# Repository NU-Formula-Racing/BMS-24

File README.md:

# BMS-24
This repo contains all the eagle and other associated hardware files for the BMS on NFR24

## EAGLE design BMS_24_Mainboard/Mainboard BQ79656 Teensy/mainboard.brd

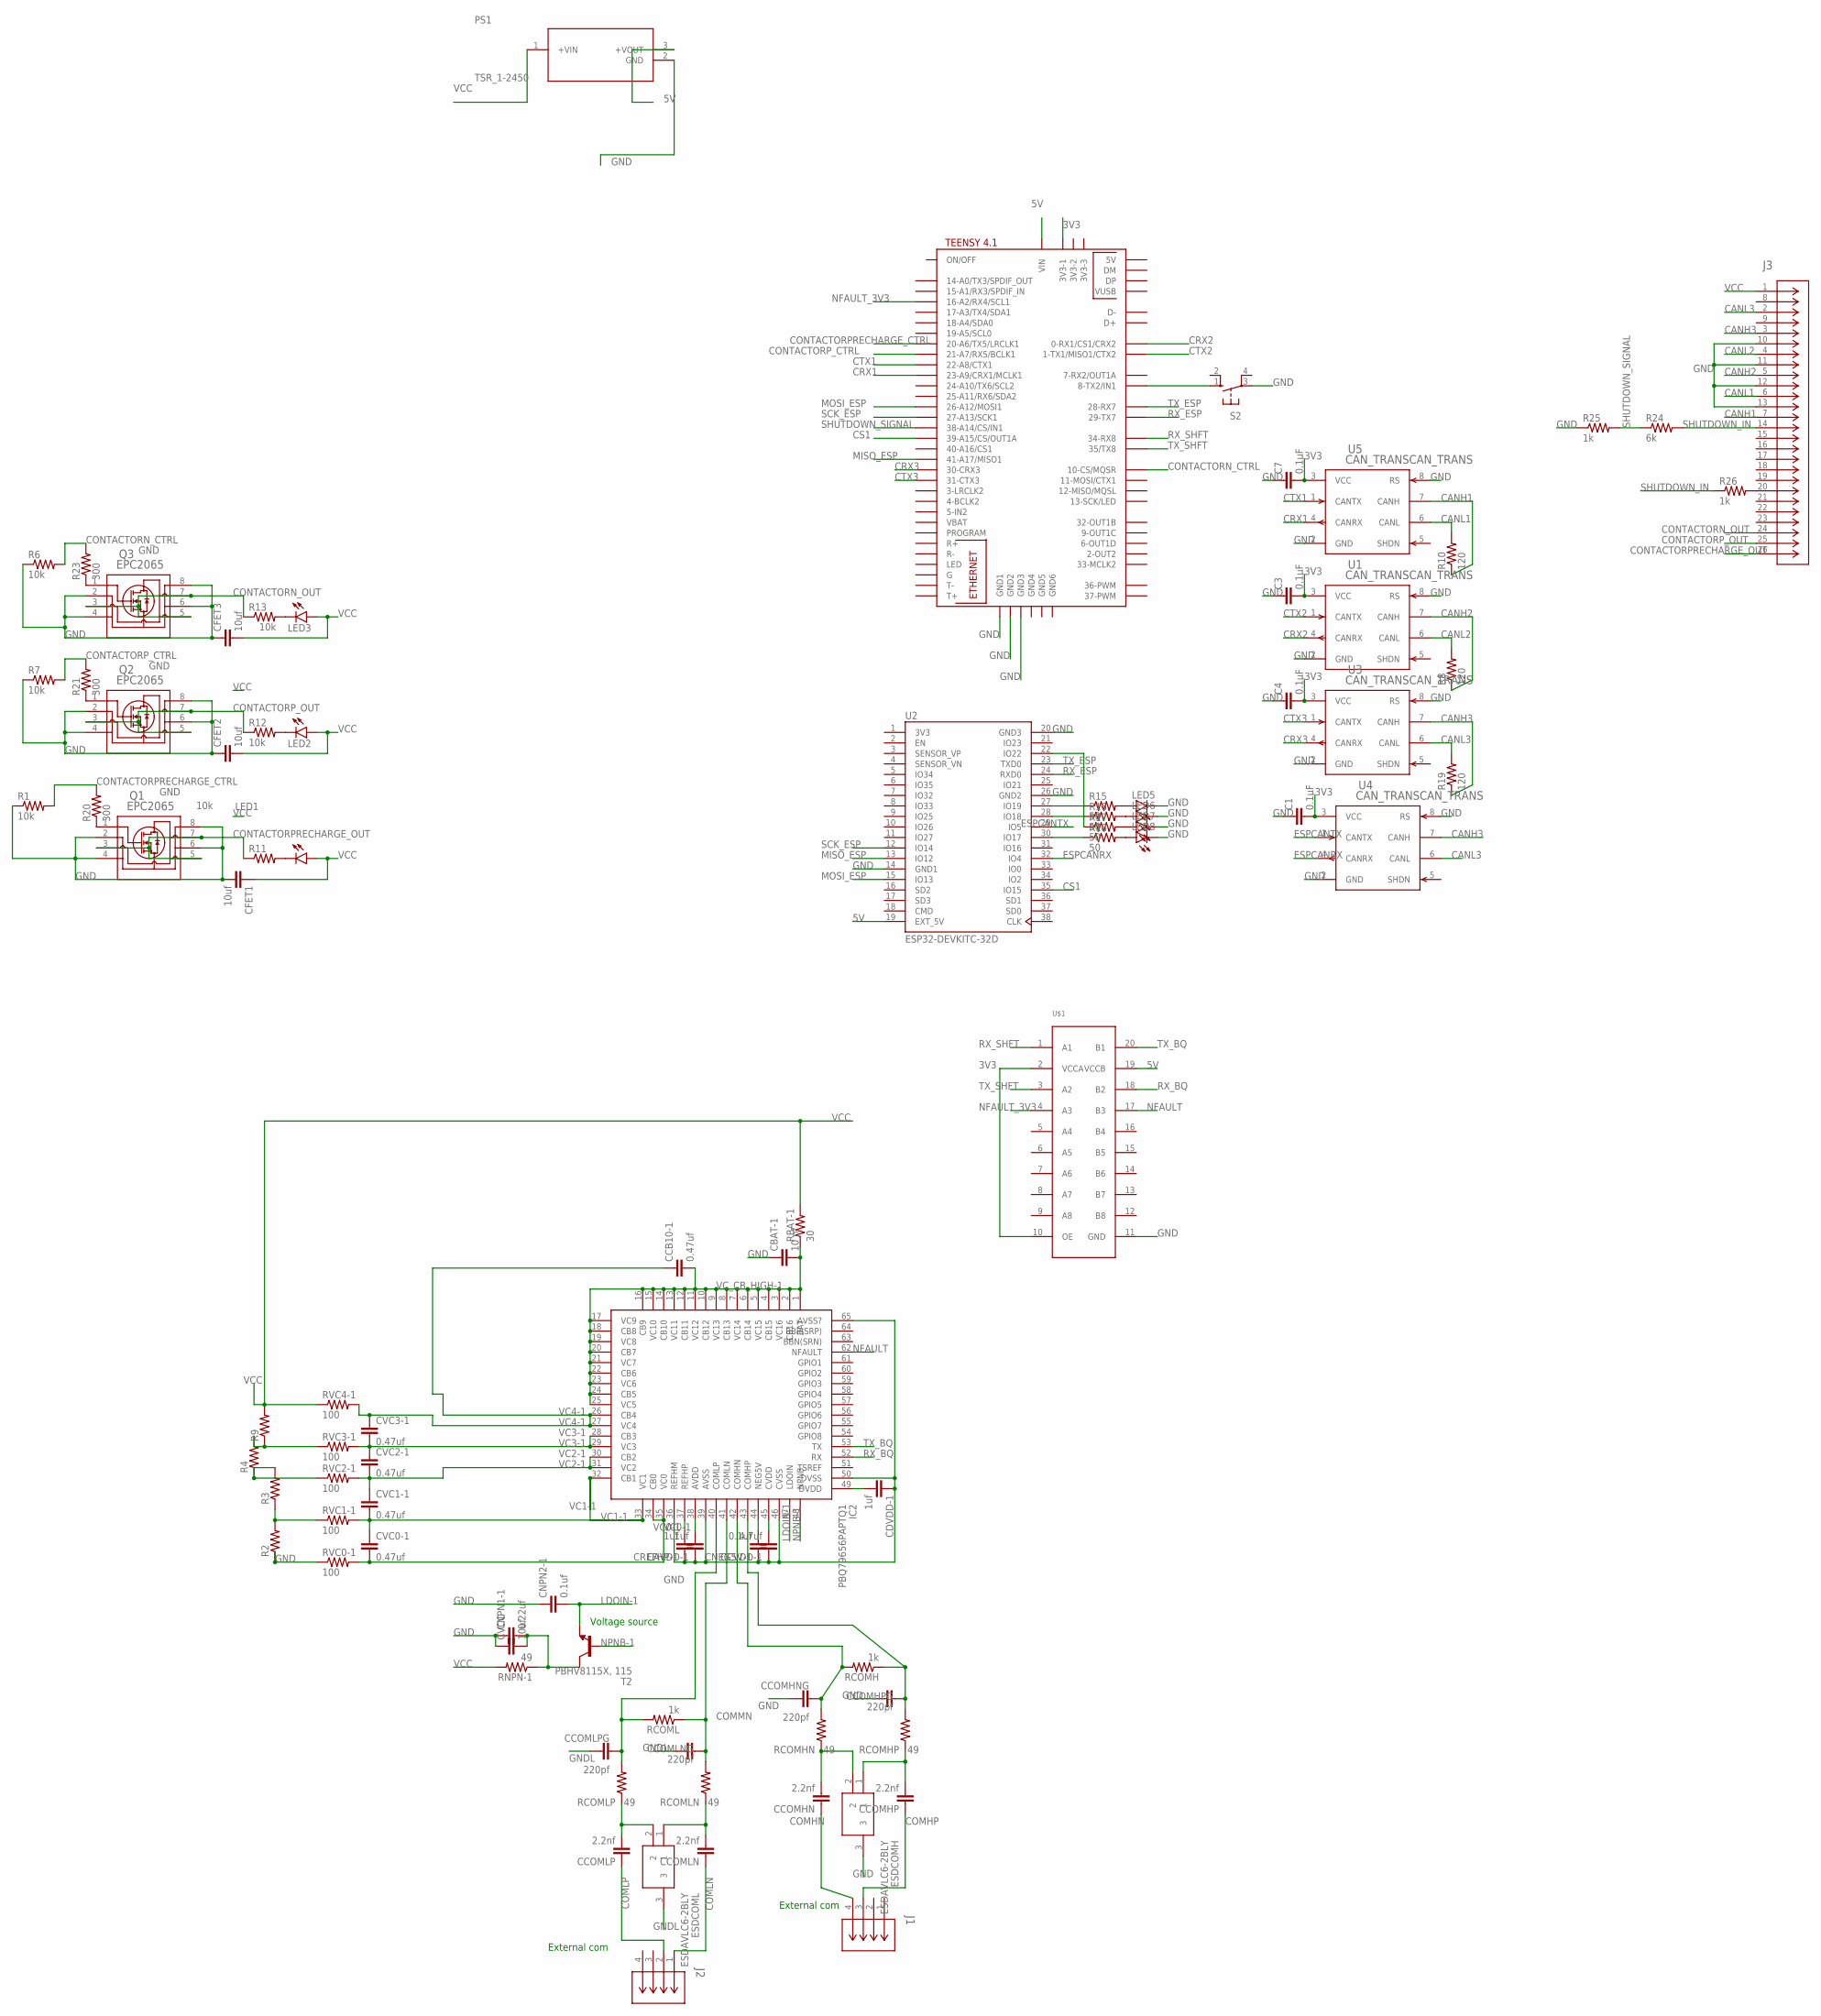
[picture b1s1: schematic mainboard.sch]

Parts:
C1, C3, C4, C7: 0.1μF; C0603
CAVDD-1: 1uf; C0603
CBAT-1: 10 nf; C0603
CCB10-1: 0.47uf; C0603
CCOMHN: 2.2nf; C075-032X103
CCOMHNG: 220pf; C0603
CCOMHP: 2.2nf; C075-032X103
CCOMHPG: 220pf; C0603
CCOMLN: 2.2nf; C075-032X103
CCOMLNG: 220pf; C0603
CCOMLP: 2.2nf; C075-032X103
CCOMLPG: 220pf; C0603
CCVDD-1: 4.7uf; C0603
CDVDD-1: 1uf; C0603
CFET1, CFET2, CFET3: 10uf; C0805
CNEG5V-1: 0.1uf; C0603
CNPN1-1: 0.22uf; C0603
CNPN2-1: 0.1uf; C0603
CREFHP-1: 1uf; C0603
CVC0-1, CVC1-1, CVC2-1, CVC3-1: 0.47uf; C0603
CVCC: 10uf; C0805
ESDCOMH: ESDAVLC6-2BLY; SOT95P255X150-3N
ESDCOML: ESDAVLC6-2BLY; SOT95P255X150-3N
IC2: PBQ79656PAPTQ1; QFP50P1200X1200X120-65N
J1, J2: DF11-4DP-2DSA(24); CON4_2X2_UF_DF11_HIR
J3: TE_AMP_SURESEAL_26; CONN26_6473423-1_TEC
LED1, LED2, LED3, LED5, LED6, LED7, LED8: LEDSML0603; SML0603
PS1: TSR_1-2450; TSR1-SINGLE_TRP
Q1, Q2, Q3: EPC2065; EPC2065_ECC
R1, R6, R7, R11, R12, R13: 10k; R0603
R2, R3, R4, R9: R-US_R0805; R0805
R8, R10, R19: 120; R0603
R15, R16, R17, R18: 50; R0603
R20, R21, R23: 300; R0603
R24: 6k; R0603
R25, R26: 1k; R0603
RBAT-1: 30; R0603
RCOMH: 1k; R0603
RCOMHN: 49; R0603
RCOMHP: 49; R0603
RCOML: 1k; R0603
RCOMLN: 49; R0603
RCOMLP: 49; R0603
RNPN-1: 49; R0603
RVC0-1, RVC1-1, RVC2-1, RVC3-1, RVC4-1: 100; R0603
S2: 10-XX; B3F-10XX
T2: PBHV8115X, 115; SOT89-BCE
U1, U3, U4, U5: CAN_TRANSCAN_TRANS; MAX3051ESA+
U2: ESP32-DEVKITC-32D; MODULE_ESP32-DEVKITC-32D
U$1: TXB0108PWSMD; TSSOP20
U$3: TEENSY41

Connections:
3V3: C1.2, C3.2, C4.2, C7.2, U1.3 (VCC), U2.1 (3V3), U3.3 (VCC), U4.3 (VCC), U5.3 (VCC), U$1.2 (VCCA), U$1.10 (OE), U$3.3V3-1
5V: PS1.3 (+VOUT), U2.19 (EXT_5V), U$1.19 (VCCB), U$3.VIN
CANH1: J3.7, R10.1, U5.7 (CANH)
CANH2: J3.5, R8.1, U1.7 (CANH)
CANH3: J3.3, R19.1, U3.7 (CANH), U4.7 (CANH)
CANL1: J3.6, R10.2, U5.6 (CANL)
CANL2: J3.4, R8.2, U1.6 (CANL)
CANL3: J3.2, R19.2, U3.6 (CANL), U4.6 (CANL)
COMHN: CCOMHN.1, J1.4
COMHP: CCOMHP.1, J1.3
COMLN: CCOMLN.1, J2.1
COMLP: CCOMLP.1, J2.2
CONTACTORN_CTRL: R6.2, R23.2, U$3.10-CS\MQSR (10-CS/MQSR)
CONTACTORN_OUT: J3.24, Q3.3, Q3.5, Q3.7, R13.1
CONTACTORPRECHARGE_CTRL: R1.2, R20.2, U$3.20-A6/TX5/LRCLK1
CONTACTORPRECHARGE_OUT: J3.26, Q1.3, Q1.5, Q1.7, R11.1
CONTACTORP_CTRL: R7.2, R21.2, U$3.21-A7/RX5/BCLK1
CONTACTORP_OUT: J3.25, Q2.3, Q2.5, Q2.7, R12.1
CRX1: U5.4 (CANRX), U$3.23-A9/CRX1/MCLK1
CRX2: U1.4 (CANRX), U$3.0-RX1/CS1/CRX2
CRX3: U3.4 (CANRX), U$3.30-CRX3
CS1: U2.35 (IO15), U$3.39-A15/CS/OUT1A
CTX1: U5.1 (CANTX), U$3.22-A8/CTX1
CTX2: U1.1 (CANTX), U$3.1-TX1/MISO1/CTX2
CTX3: U3.1 (CANTX), U$3.31-CTX3
CVDD-1: CCVDD-1.2, IC2.45 (CVDD)
ESPCANRX: U2.32 (IO4), U4.4 (CANRX)
ESPCANTX: U2.29 (IO5), U4.1 (CANTX)
GND: C1.1, C3.1, C4.1, C7.1, CAVDD-1.1, CBAT-1.1, CCOMHNG.1, CCOMHPG.1, CCVDD-1.1, CDVDD-1.1, CFET1.2, CFET2.1, CFET3.1, CNEG5V-1.1, CNPN1-1.1, CNPN2-1.1, CREFHP-1.1, CVCC.1, ESDCOMH.3, IC2.36 (REFHM), IC2.39 (AVSS), IC2.46 (CVSS), IC2.50 (DVSS), IC2.65 (AVSS?), J3.10, J3.11, J3.12, J3.13, LED5.C, LED6.C, LED7.C, LED8.C, PS1.2 (GND), Q1.2, Q1.4, Q1.6, Q1.8, Q2.2, Q2.4, Q2.6, Q2.8, Q3.2, Q3.4, Q3.6, Q3.8, R1.1, R2.1, R6.1, R7.1, R25.1, RVC0-1.1, S2.3, U1.2 (GND), U1.8 (RS), U2.14 (GND1), U2.20 (GND3), U2.26 (GND2), U3.2 (GND), U3.8 (RS), U4.2 (GND), U4.8 (RS), U5.2 (GND), U5.8 (RS), U$1.11 (GND), U$3.GND1, U$3.GND2, U$3.GND3
GNDL: CCOMLNG.1, CCOMLPG.1, ESDCOML.3
LDOIN-1: CNPN2-1.2, IC2.47 (LDOIN), T2.E
MISO_ESP: U2.13 (IO12), U$3.41-A17/MISO1
MOSI_ESP: U2.15 (IO13), U$3.26-A12/MOSI1
unnamed: CCOMHP.2, ESDCOMH.1, RCOMHP.1
unnamed: J3.20, R26.2
unnamed: LED3.C, R13.2
unnamed: S2.1 (S), U$3.8-TX2/IN1
unnamed: CCOMHN.2, ESDCOMH.2, RCOMHN.1
unnamed: LED2.C, R12.2
unnamed: CCOMLNG.2, IC2.41 (COMLN), RCOML.1, RCOMLN.2
unnamed: R17.1, U2.22 (IO22)
unnamed: LED1.C, R11.2
unnamed: Q1.1, R20.1
unnamed: Q2.1, R21.1
unnamed: R15.1, U2.27 (IO19)
unnamed: R16.1, U2.28 (IO18)
unnamed: Q3.1, R23.1
unnamed: R18.1, U2.30 (IO17)
unnamed: LED5.A, R15.2
unnamed: LED6.A, R16.2
unnamed: LED7.A, R17.2
unnamed: LED8.A, R18.2
unnamed: CCOMLPG.2, IC2.40 (COMLP), RCOML.2, RCOMLP.2
unnamed: CCOMLP.2, ESDCOML.2, RCOMLP.1
unnamed: CCOMLN.2, ESDCOML.1, RCOMLN.1
unnamed: R3.2, R4.1, RVC2-1.1
unnamed: R2.2, R3.1, RVC1-1.1
unnamed: R4.2, R9.1, RVC3-1.1
unnamed: CREFHP-1.2, IC2.37 (REFHP)
unnamed: CAVDD-1.2, IC2.38 (AVDD)
unnamed: CNEG5V-1.2, IC2.44 (NEG5V)
unnamed: CDVDD-1.2, IC2.49 (DVDD)
unnamed: CNPN1-1.2, CVCC.2, RNPN-1.1, T2.C
unnamed: CCOMHPG.2, IC2.43 (COMHP), RCOMH.1, RCOMHP.2
unnamed: CCOMHNG.2, IC2.42 (COMHN), RCOMH.2, RCOMHN.2
NFAULT: IC2.62 (NFAULT), U$1.17 (B3)
NFAULT_3V3: U$1.4 (A3), U$3.16-A2/RX4/SCL1
NPNB-1: IC2.48 (NPNB), T2.B
RX_BQ: IC2.52 (RX), U$1.18 (B2)
RX_ESP: U2.24 (RXD0), U$3.29-TX7
RX_SHFT: U$1.1 (A1), U$3.34-RX8
SCK_ESP: U2.12 (IO14), U$3.27-A13/SCK1
SHUTDOWN_IN: J3.14, R24.2, R26.1
SHUTDOWN_SIGNAL: R24.1, R25.2, U$3.38-A14/CS/IN1
TX_BQ: IC2.53 (TX), U$1.20 (B1)
TX_ESP: U2.23 (TXD0), U$3.28-RX7
TX_SHFT: U$1.3 (A2), U$3.35-TX8 (35/TX8)
VC0-1: CVC0-1.2, IC2.34 (CB0), IC2.35 (VC0), RVC0-1.2
VC1-1: CVC0-1.1, CVC1-1.2, IC2.32 (CB1), IC2.33 (VC1), RVC1-1.2
VC2-1: CVC1-1.1, CVC2-1.2, IC2.30 (CB2), IC2.31 (VC2), RVC2-1.2
VC3-1: CVC2-1.1, CVC3-1.2, IC2.28 (CB3), IC2.29 (VC3), RVC3-1.2
VC4-1: CCB10-1.1, CVC3-1.1, IC2.26 (CB4), IC2.27 (VC4), RVC4-1.2
VCC: CFET1.1, CFET2.2, CFET3.2, J3.1, LED1.A, LED2.A, LED3.A, PS1.1 (+VIN), R9.2, RBAT-1.2, RNPN-1.2, RVC4-1.1
VC_CB_HIGH-1: CBAT-1.2, CCB10-1.2, IC2.1 (BAT), IC2.2 (CB16), IC2.3 (VC16), IC2.4 (CB15), IC2.5 (VC15), IC2.6 (CB14), IC2.7 (VC14), IC2.8 (CB13), IC2.9 (VC13), IC2.10 (CB12), IC2.11 (VC12), IC2.12 (CB11), IC2.13 (VC11), IC2.14 (CB10), IC2.15 (VC10), IC2.16 (CB9), IC2.17 (VC9), IC2.18 (CB8), IC2.19 (VC8), IC2.20 (CB7), IC2.21 (VC7), IC2.22 (CB6), IC2.23 (VC6), IC2.24 (CB5), IC2.25 (VC5), RBAT-1.1

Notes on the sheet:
External com
Voltage source

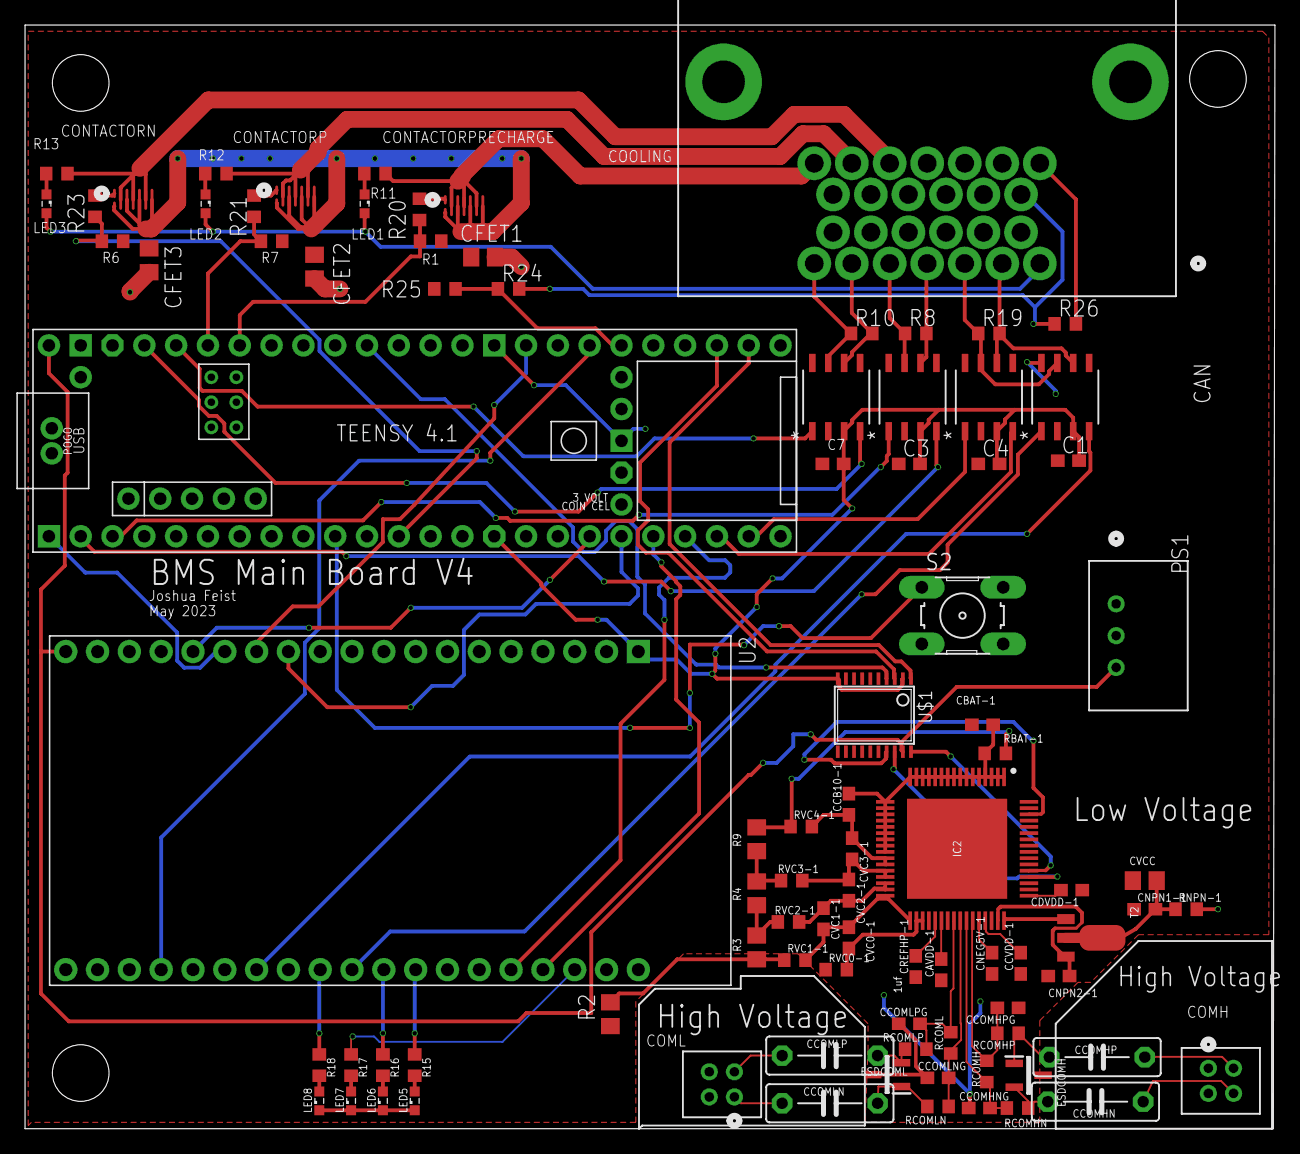
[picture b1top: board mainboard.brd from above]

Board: 2 copper layers, 99.8 x 88.1 mm, 91 parts (0 on the bottom side), 84 nets.

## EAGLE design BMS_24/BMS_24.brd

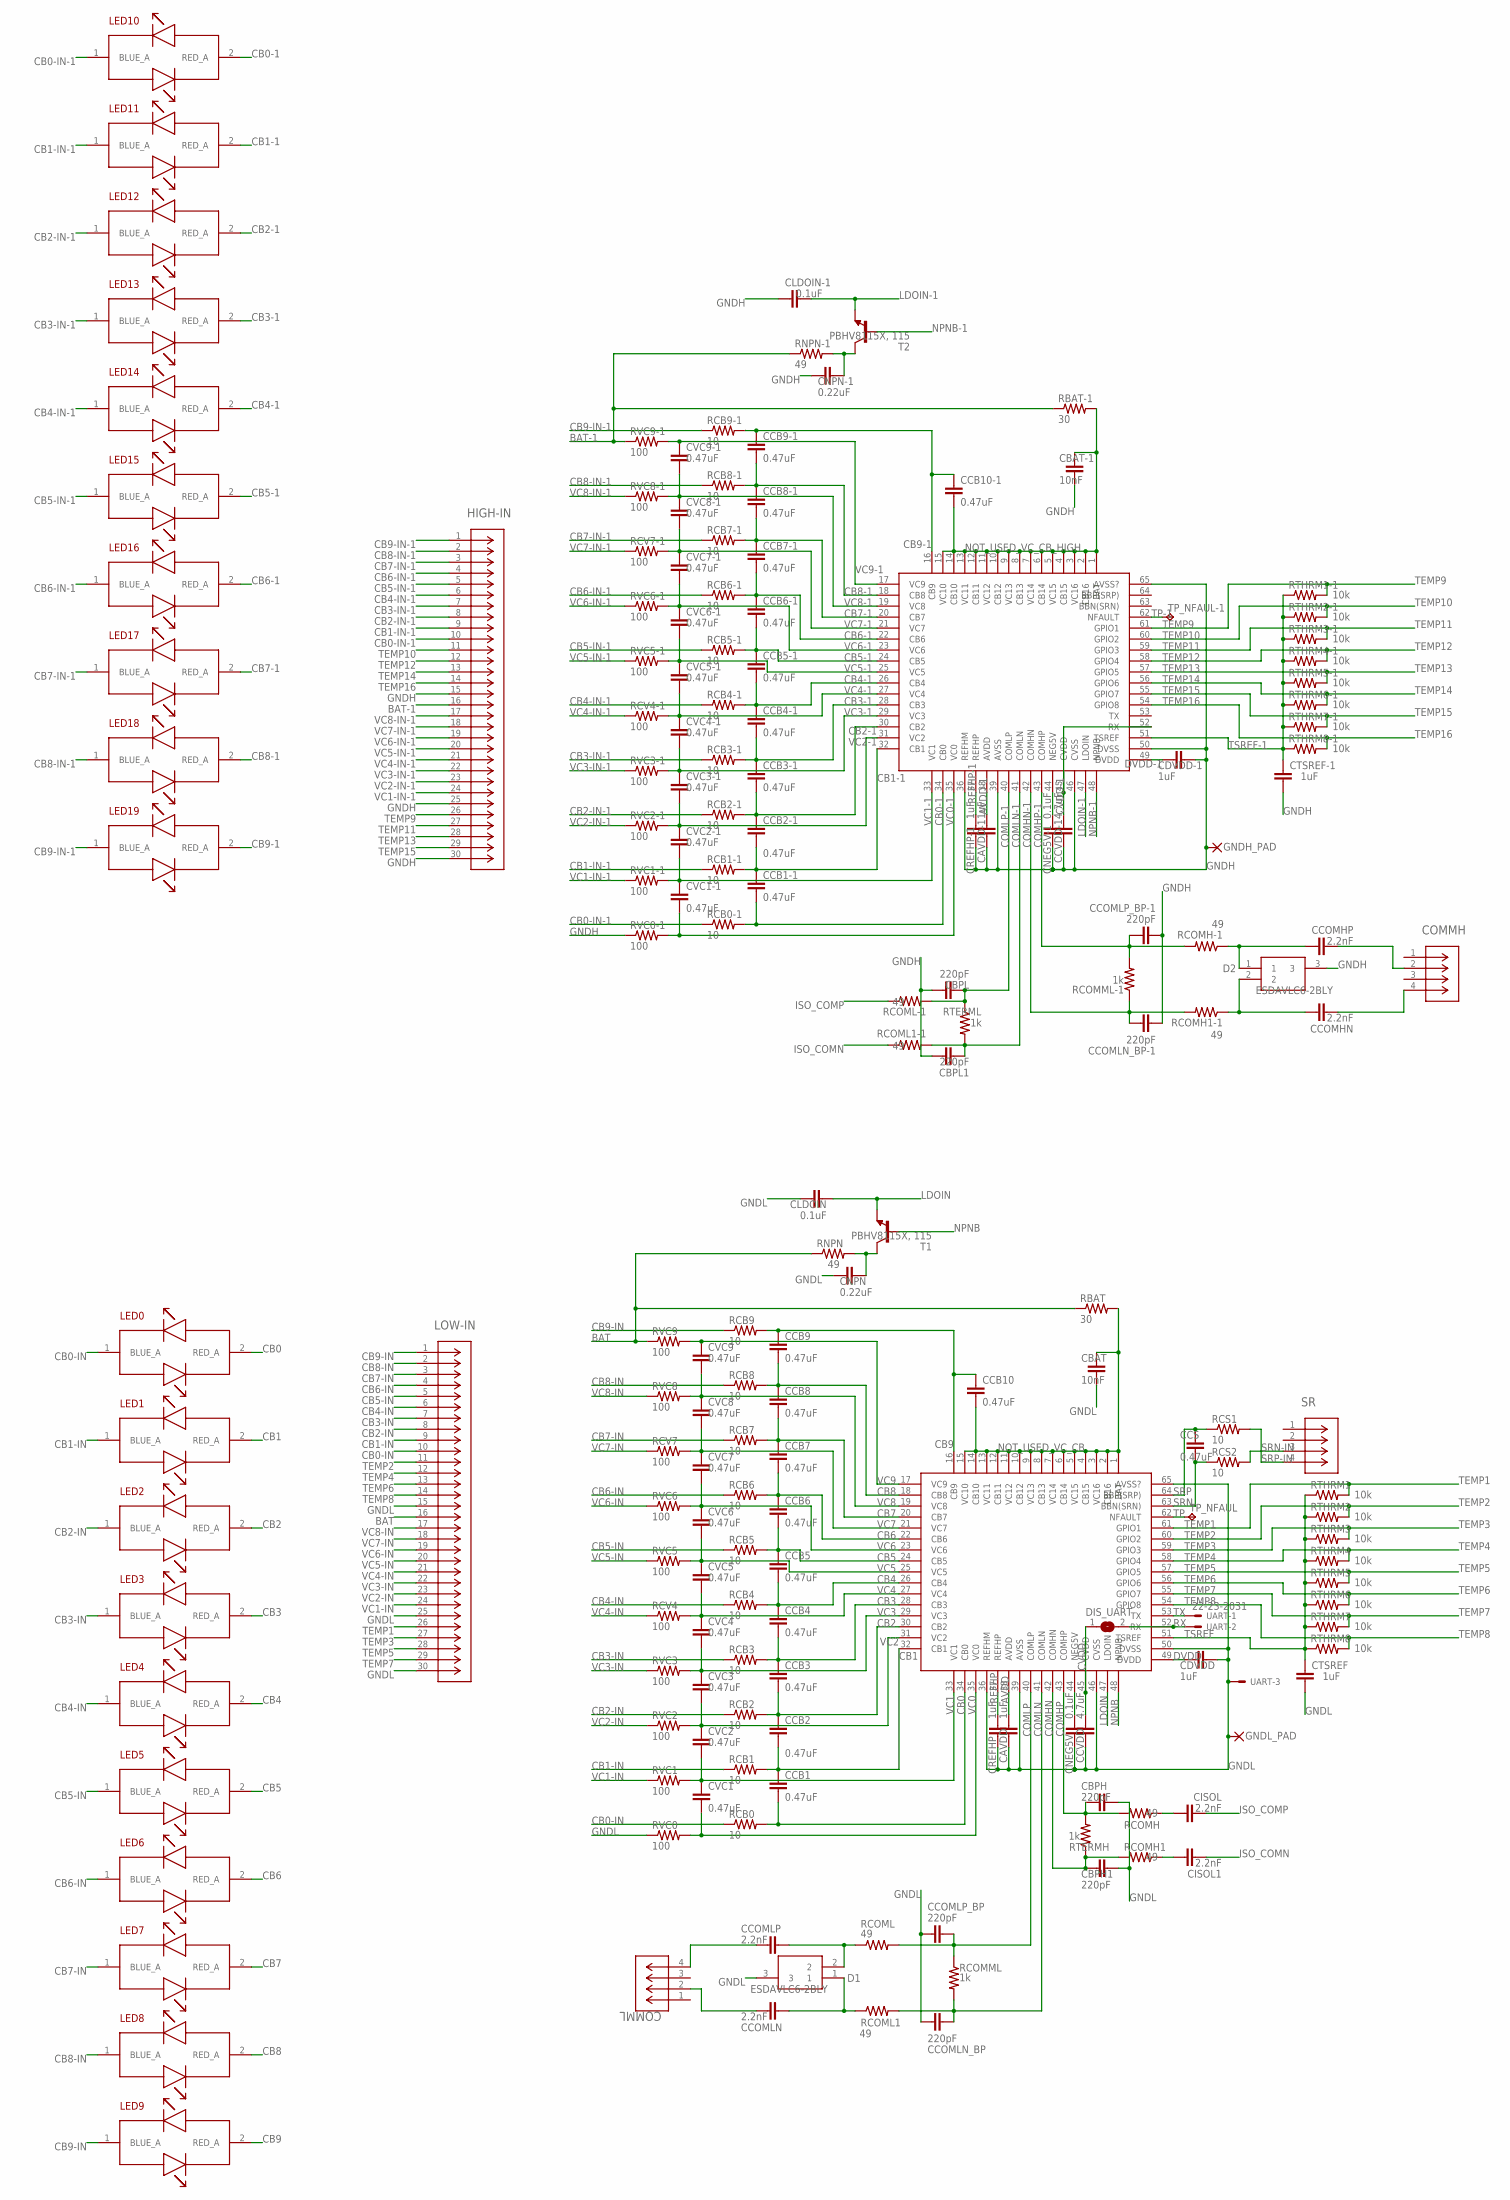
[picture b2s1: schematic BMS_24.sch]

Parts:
CAVDD: 1uF; C0603
CAVDD-1: 1uF; C0603
CBAT: 10nF; C0603
CBAT-1: 10nF; C0603
CBPH, CBPH1: 220pF; C0603
CBPL, CBPL1: 220pF; C0603
CCB1, CCB1-1, CCB2, CCB2-1, CCB3, CCB3-1, CCB4, CCB4-1, CCB5, CCB5-1, CCB6, CCB6-1, CCB7, CCB7-1, CCB8, CCB8-1, CCB9, CCB9-1, CCB10, CCB10-1: 0.47uF; C0603
CCOMHN: 2.2nF; C0603
CCOMHP: 2.2nF; C0603
CCOMLN: 2.2nF; C0603
CCOMLN_BP: 220pF; C0603
CCOMLN_BP-1: 220pF; C0603
CCOMLP: 2.2nF; C0603
CCOMLP_BP: 220pF; C0603
CCOMLP_BP-1: 220pF; C0603
CCS: 0.47uF; C0603
CCVDD: 4.7uF; C0603
CCVDD-1: 4.7uF; C0603
CDVDD: 1uF; C0603
CDVDD-1: 1uF; C0603
CISOL, CISOL1: 2.2nF; C0603
CLDOIN: 0.1uF; C0603
CLDOIN-1: 0.1uF; C0603
CNEG5V, CNEG5V-1: 0.1uF; C0603
CNPN: 0.22uF; C0603
CNPN-1: 0.22uF; C0603
COMMH: DF11-4DP-2DSA(24); CON4_2X2_UF_DF11_HIR
COMML: DF11-4DP-2DSA(24); CON4_2X2_UF_DF11_HIR
CREFHP: 1uF; C0603
CREFHP-1: 1uF; C0603
CTSREF: 1uF; C0603
CTSREF-1: 1uF; C0603
CVC1, CVC1-1, CVC2, CVC2-1, CVC3, CVC3-1, CVC4, CVC4-1, CVC5, CVC5-1, CVC6, CVC6-1, CVC7, CVC7-1, CVC8, CVC8-1, CVC9, CVC9-1: 0.47uF; C0603
D1, D2: ESDAVLC6-2BLY; SOT95P255X150-3N
DIS_UART: SJ
GNDH_PAD: SMD2; SMD1,27-2,54
GNDL_PAD: SMD2; SMD1,27-2,54
HIGH-IN: 87606-315LF; 87606-315LF_AMP
IC1, IC2: PBQ79656PAPTQ1; QFP50P1200X1200X120-65N
LED0, LED1, LED2, LED3, LED4, LED5, LED6, LED7, LED8, LED9, LED10, LED11, LED12, LED13, LED14, LED15, LED16, LED17, LED18, LED19: TJ-S1608SW6TNPGLCRB-A5
LOW-IN: 87606-315LF; 87606-315LF_AMP
RBAT: 30; R0603
RBAT-1: 30; R0603
RCB0, RCB0-1, RCB1, RCB1-1, RCB2, RCB2-1, RCB3, RCB3-1, RCB4, RCB4-1, RCB5, RCB5-1, RCB6, RCB6-1, RCB7, RCB7-1, RCB8, RCB8-1, RCB9, RCB9-1: 10; R1210
RCOMH, RCOMH1, RCOMH1-1: 49; R0603
RCOMH-1: 49; R0603
RCOML, RCOML1, RCOML1-1: 49; R0603
RCOML-1: 49; R0603
RCOMML: 1k; R0603
RCOMML-1: 1k; R0603
RCS1, RCS2: 10; R0603
RCV4, RCV4-1, RCV7, RCV7-1: 100; R0603
RNPN: 49; R0603
RNPN-1: 49; R0603
RTERMH: 1k; R0603
RTERML: 1k; R0603
RTHRM1, RTHRM1-1, RTHRM2, RTHRM2-1, RTHRM3, RTHRM3-1, RTHRM4, RTHRM4-1, RTHRM5, RTHRM5-1, RTHRM6, RTHRM6-1, RTHRM7, RTHRM7-1, RTHRM8, RTHRM8-1: 10k; R0603
RVC0, RVC0-1, RVC1, RVC1-1, RVC2, RVC2-1, RVC3, RVC3-1, RVC5, RVC5-1, RVC6, RVC6-1, RVC8, RVC8-1, RVC9, RVC9-1: 100; R0603
SR: DF11-4DP-2DSA(24); CON4_2X2_UF_DF11_HIR
T1, T2: PBHV8115X, 115; SOT89-BCE
TP_NFAUL: TPB2,54; B2,54
TP_NFAUL-1: TPB2,54; B2,54
UART: 22-23-2031

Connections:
AVDD: CAVDD.1, IC2.38 (AVDD)
AVDD-1: CAVDD-1.1, IC1.38 (AVDD)
BAT: LOW-IN.16, RBAT.1, RNPN.1, RVC9.1
BAT-1: HIGH-IN.16, RBAT-1.1, RNPN-1.1, RVC9-1.1
CB0: CCB1.2, IC2.34 (CB0), LED0.2 (RED_A), RCB0.2
CB0-1: CCB1-1.2, IC1.34 (CB0), LED10.2 (RED_A), RCB0-1.2
CB0-IN: LED0.1 (BLUE_A), LOW-IN.10, RCB0.1
CB0-IN-1: HIGH-IN.10, LED10.1 (BLUE_A), RCB0-1.1
CB1: CCB1.1, CCB2.2, IC2.32 (CB1), LED1.2 (RED_A), RCB1.2
CB1-1: CCB1-1.1, CCB2-1.2, IC1.32 (CB1), LED11.2 (RED_A), RCB1-1.2
CB1-IN: LED1.1 (BLUE_A), LOW-IN.9, RCB1.1
CB1-IN-1: HIGH-IN.9, LED11.1 (BLUE_A), RCB1-1.1
CB2: CCB2.1, CCB3.2, IC2.30 (CB2), LED2.2 (RED_A), RCB2.2
CB2-1: CCB2-1.1, CCB3-1.2, IC1.30 (CB2), LED12.2 (RED_A), RCB2-1.2
CB2-IN: LED2.1 (BLUE_A), LOW-IN.8, RCB2.1
CB2-IN-1: HIGH-IN.8, LED12.1 (BLUE_A), RCB2-1.1
CB3: CCB3.1, CCB4.2, IC2.28 (CB3), LED3.2 (RED_A), RCB3.2
CB3-1: CCB3-1.1, CCB4-1.2, IC1.28 (CB3), LED13.2 (RED_A), RCB3-1.2
CB3-IN: LED3.1 (BLUE_A), LOW-IN.7, RCB3.1
CB3-IN-1: HIGH-IN.7, LED13.1 (BLUE_A), RCB3-1.1
CB4: CCB4.1, CCB5.2, IC2.26 (CB4), LED4.2 (RED_A), RCB4.2
CB4-1: CCB4-1.1, CCB5-1.2, IC1.26 (CB4), LED14.2 (RED_A), RCB4-1.2
CB4-IN: LED4.1 (BLUE_A), LOW-IN.6, RCB4.1
CB4-IN-1: HIGH-IN.6, LED14.1 (BLUE_A), RCB4-1.1
CB5: CCB5.1, CCB6.2, IC2.24 (CB5), LED5.2 (RED_A), RCB5.2
CB5-1: CCB5-1.1, CCB6-1.2, IC1.24 (CB5), LED15.2 (RED_A), RCB5-1.2
CB5-IN: LED5.1 (BLUE_A), LOW-IN.5, RCB5.1
CB5-IN-1: HIGH-IN.5, LED15.1 (BLUE_A), RCB5-1.1
CB6: CCB6.1, CCB7.2, IC2.22 (CB6), LED6.2 (RED_A), RCB6.2
CB6-1: CCB6-1.1, CCB7-1.2, IC1.22 (CB6), LED16.2 (RED_A), RCB6-1.2
CB6-IN: LED6.1 (BLUE_A), LOW-IN.4, RCB6.1
CB6-IN-1: HIGH-IN.4, LED16.1 (BLUE_A), RCB6-1.1
CB7: CCB7.1, CCB8.2, IC2.20 (CB7), LED7.2 (RED_A), RCB7.2
CB7-1: CCB7-1.1, CCB8-1.2, IC1.20 (CB7), LED17.2 (RED_A), RCB7-1.2
CB7-IN: LED7.1 (BLUE_A), LOW-IN.3, RCB7.1
CB7-IN-1: HIGH-IN.3, LED17.1 (BLUE_A), RCB7-1.1
CB8: CCB8.1, CCB9.2, IC2.18 (CB8), LED8.2 (RED_A), RCB8.2
CB8-1: CCB8-1.1, CCB9-1.2, IC1.18 (CB8), LED18.2 (RED_A), RCB8-1.2
CB8-IN: LED8.1 (BLUE_A), LOW-IN.2, RCB8.1
CB8-IN-1: HIGH-IN.2, LED18.1 (BLUE_A), RCB8-1.1
CB9: CCB9.1, CCB10.2, IC2.16 (CB9), LED9.2 (RED_A), RCB9.2
CB9-1: CCB9-1.1, CCB10-1.2, IC1.16 (CB9), LED19.2 (RED_A), RCB9-1.2
CB9-IN: LED9.1 (BLUE_A), LOW-IN.1, RCB9.1
CB9-IN-1: HIGH-IN.1, LED19.1 (BLUE_A), RCB9-1.1
COMHN: CBPH1.1, IC2.42 (COMHN), RCOMH1.2, RTERMH.1
COMHN-1: CCOMLN_BP-1.1, IC1.42 (COMHN), RCOMH1-1.2, RCOMML-1.1
COMHP: CBPH.1, IC2.43 (COMHP), RCOMH.2, RTERMH.2
COMHP-1: CCOMLP_BP-1.1, IC1.43 (COMHP), RCOMH-1.2, RCOMML-1.2
COMLN: CCOMLN_BP.1, IC2.41 (COMLN), RCOML1.2, RCOMML.2
COMLN-1: CBPL1.1, IC1.41 (COMLN), RCOML1-1.2, RTERML.2
COMLP: CCOMLP_BP.1, IC2.40 (COMLP), RCOML.2, RCOMML.1
COMLP-1: CBPL.1, IC1.40 (COMLP), RCOML-1.2, RTERML.1
CVDD: CCVDD.1, DIS_UART.1, IC2.45 (CVDD)
CVDD-1: CCVDD-1.1, IC1.45 (CVDD), IC1.52 (RX)
DVDD: CDVDD.1, IC2.49 (DVDD)
DVDD-1: CDVDD-1.1, IC1.49 (DVDD)
GNDH: CAVDD-1.2, CBAT-1.1, CBPL.2, CBPL1.2, CCOMLN_BP-1.2, CCOMLP_BP-1.2, CCVDD-1.2, CDVDD-1.2, CLDOIN-1.2, CNEG5V-1.2, CNPN-1.1, CREFHP-1.2, CTSREF-1.2, D2.3, GNDH_PAD.1, HIGH-IN.15, HIGH-IN.25, HIGH-IN.30, IC1.36 (REFHM), IC1.39 (AVSS), IC1.46 (CVSS), IC1.50 (DVSS), IC1.65 (AVSS?), RVC0-1.1
GNDL: CAVDD.2, CBAT.1, CBPH.2, CBPH1.2, CCOMLN_BP.2, CCOMLP_BP.2, CCVDD.2, CDVDD.2, CLDOIN.2, CNEG5V.2, CNPN.1, CREFHP.2, CTSREF.2, D1.3, GNDL_PAD.1, IC2.36 (REFHM), IC2.39 (AVSS), IC2.46 (CVSS), IC2.50 (DVSS), IC2.65 (AVSS?), LOW-IN.15, LOW-IN.25, LOW-IN.30, RVC0.1, UART.3
ISO_COMN: CISOL1.1, RCOML1-1.1
ISO_COMP: CISOL.1, RCOML-1.1
LDOIN: CLDOIN.1, IC2.47 (LDOIN), T1.E
LDOIN-1: CLDOIN-1.1, IC1.47 (LDOIN), T2.E
unnamed: CNPN.2, RNPN.2, T1.C
unnamed: CNEG5V.1, IC2.44 (NEG5V)
unnamed: CISOL.2, RCOMH.1
unnamed: CISOL1.2, RCOMH1.1
unnamed: CCOMLN.2, D1.1, RCOML1.1
unnamed: CCOMLP.2, D1.2, RCOML.1
unnamed: CNEG5V-1.1, IC1.44 (NEG5V)
unnamed: CNPN-1.2, RNPN-1.2, T2.C
unnamed: CCOMHP.2, D2.1, RCOMH-1.1
unnamed: CCOMHN.2, D2.2, RCOMH1-1.1
unnamed: CCOMHP.1, COMMH.2
unnamed: CCOMHN.1, COMMH.4
unnamed: CCOMLN.1, COMML.2
unnamed: CCOMLP.1, COMML.4
NOT_USED_VC_CB: CBAT.2, CCB10.1, IC2.1 (BAT), IC2.2 (CB16), IC2.3 (VC16), IC2.4 (CB15), IC2.5 (VC15), IC2.6 (CB14), IC2.7 (VC14), IC2.8 (CB13), IC2.9 (VC13), IC2.10 (CB12), IC2.11 (VC12), IC2.12 (CB11), IC2.13 (VC11), IC2.14 (CB10), IC2.15 (VC10), RBAT.2
NOT_USED_VC_CB_HIGH: CBAT-1.2, CCB10-1.1, IC1.1 (BAT), IC1.2 (CB16), IC1.3 (VC16), IC1.4 (CB15), IC1.5 (VC15), IC1.6 (CB14), IC1.7 (VC14), IC1.8 (CB13), IC1.9 (VC13), IC1.10 (CB12), IC1.11 (VC12), IC1.12 (CB11), IC1.13 (VC11), IC1.14 (CB10), IC1.15 (VC10), RBAT-1.2
NPNB: IC2.48 (NPNB), T1.B
NPNB-1: IC1.48 (NPNB), T2.B
REFHP: CREFHP.1, IC2.37 (REFHP)
REFHP-1: CREFHP-1.1, IC1.37 (REFHP)
RX: DIS_UART.2, IC2.52 (RX), UART.2
SRN: CCS.1, IC2.63 (BBN(SRN)), RCS2.1
SRN-IN: RCS2.2, SR.3
SRP: CCS.2, IC2.64 (BBP(SRP)), RCS1.1
SRP-IN: RCS1.2, SR.4
TEMP1: IC2.61 (GPIO1), LOW-IN.26, RTHRM1.2
TEMP2: IC2.60 (GPIO2), LOW-IN.11, RTHRM2.2
TEMP3: IC2.59 (GPIO3), LOW-IN.27, RTHRM3.2
TEMP4: IC2.58 (GPIO4), LOW-IN.12, RTHRM4.2
TEMP5: IC2.57 (GPIO5), LOW-IN.28, RTHRM5.2
TEMP6: IC2.56 (GPIO6), LOW-IN.13, RTHRM6.2
TEMP7: IC2.55 (GPIO7), LOW-IN.29, RTHRM7.2
TEMP8: IC2.54 (GPIO8), LOW-IN.14, RTHRM8.2
TEMP9: HIGH-IN.26, IC1.61 (GPIO1), RTHRM1-1.2
TEMP10: HIGH-IN.11, IC1.60 (GPIO2), RTHRM2-1.2
TEMP11: HIGH-IN.27, IC1.59 (GPIO3), RTHRM3-1.2
TEMP12: HIGH-IN.12, IC1.58 (GPIO4), RTHRM4-1.2
TEMP13: HIGH-IN.28, IC1.57 (GPIO5), RTHRM5-1.2
TEMP14: HIGH-IN.13, IC1.56 (GPIO6), RTHRM6-1.2
TEMP15: HIGH-IN.29, IC1.55 (GPIO7), RTHRM7-1.2
TEMP16: HIGH-IN.14, IC1.54 (GPIO8), RTHRM8-1.2
TP: IC2.62 (NFAULT), TP_NFAUL.TP
TP-1: IC1.62 (NFAULT), TP_NFAUL-1.TP
TSREF: CTSREF.1, IC2.51 (TSREF), RTHRM1.1, RTHRM2.1, RTHRM3.1, RTHRM4.1, RTHRM5.1, RTHRM6.1, RTHRM7.1, RTHRM8.1
TSREF-1: CTSREF-1.1, IC1.51 (TSREF), RTHRM1-1.1, RTHRM2-1.1, RTHRM3-1.1, RTHRM4-1.1, RTHRM5-1.1, RTHRM6-1.1, RTHRM7-1.1, RTHRM8-1.1
TX: IC2.53 (TX), UART.1
VC0: CVC1.2, IC2.35 (VC0), RVC0.2
VC0-1: CVC1-1.2, IC1.35 (VC0), RVC0-1.2
VC1: CVC1.1, CVC2.2, IC2.33 (VC1), RVC1.2
VC1-1: CVC1-1.1, CVC2-1.2, IC1.33 (VC1), RVC1-1.2
VC1-IN: LOW-IN.24, RVC1.1
VC1-IN-1: HIGH-IN.24, RVC1-1.1
VC2: CVC2.1, CVC3.2, IC2.31 (VC2), RVC2.2
VC2-1: CVC2-1.1, CVC3-1.2, IC1.31 (VC2), RVC2-1.2
VC2-IN: LOW-IN.23, RVC2.1
VC2-IN-1: HIGH-IN.23, RVC2-1.1
VC3: CVC3.1, CVC4.2, IC2.29 (VC3), RVC3.2
VC3-1: CVC3-1.1, CVC4-1.2, IC1.29 (VC3), RVC3-1.2
VC3-IN: LOW-IN.22, RVC3.1
VC3-IN-1: HIGH-IN.22, RVC3-1.1
VC4: CVC4.1, CVC5.2, IC2.27 (VC4), RCV4.2
VC4-1: CVC4-1.1, CVC5-1.2, IC1.27 (VC4), RCV4-1.2
VC4-IN: LOW-IN.21, RCV4.1
VC4-IN-1: HIGH-IN.21, RCV4-1.1
VC5: CVC5.1, CVC6.2, IC2.25 (VC5), RVC5.2
VC5-1: CVC5-1.1, CVC6-1.2, IC1.25 (VC5), RVC5-1.2
VC5-IN: LOW-IN.20, RVC5.1
VC5-IN-1: HIGH-IN.20, RVC5-1.1
VC6: CVC6.1, CVC7.2, IC2.23 (VC6), RVC6.2
VC6-1: CVC6-1.1, CVC7-1.2, IC1.23 (VC6), RVC6-1.2
VC6-IN: LOW-IN.19, RVC6.1
VC6-IN-1: HIGH-IN.19, RVC6-1.1
VC7: CVC7.1, CVC8.2, IC2.21 (VC7), RCV7.2
VC7-1: CVC7-1.1, CVC8-1.2, IC1.21 (VC7), RCV7-1.2
VC7-IN: LOW-IN.18, RCV7.1
VC7-IN-1: HIGH-IN.18, RCV7-1.1
VC8: CVC8.1, CVC9.2, IC2.19 (VC8), RVC8.2
VC8-1: CVC8-1.1, CVC9-1.2, IC1.19 (VC8), RVC8-1.2
VC8-IN: LOW-IN.17, RVC8.1
VC8-IN-1: HIGH-IN.17, RVC8-1.1
VC9: CVC9.1, IC2.17 (VC9), RVC9.2
VC9-1: CVC9-1.1, IC1.17 (VC9), RVC9-1.2

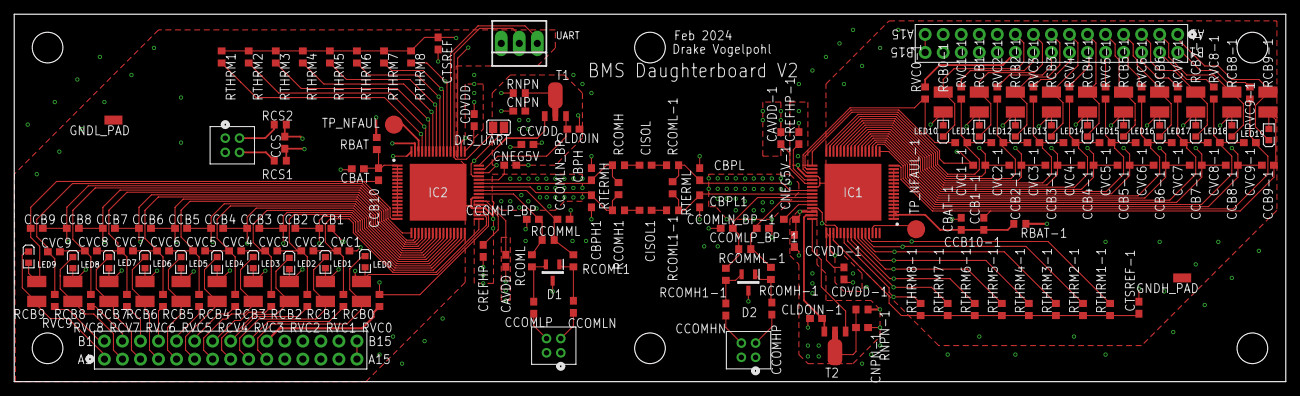
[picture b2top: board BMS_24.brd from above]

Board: 4 copper layers, 179.1 x 51.7 mm, 182 parts (0 on the bottom side), 144 nets.

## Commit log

2024-06-13 Added V2 files for mainboard

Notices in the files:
parts and their libraries:
COPYRIGHT: Copyright (C) 2023 Ultra Librarian. All rights reserved.
COPYRIGHT: Copyright (C) 2024 Ultra Librarian. All rights reserved.
COPYRIGHT: Copyright (C) 2022 Ultra Librarian. All rights reserved.
